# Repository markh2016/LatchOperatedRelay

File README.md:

# LatchOperatedRelay
Basic operating system requirements 

# PCB Layout

# Schematic Layout 

Cad software used  KICAD 

Version: 6.0.11+dfsg-1, release build
Libraries:
    wxWidgets 3.2.2
    libcurl/7.88.1 OpenSSL/3.0.9 zlib/1.2.13 brotli/1.0.9 zstd/1.5.4 libidn2/2.3.3 libpsl/0.21.2 (+libidn2/2.3.3) libssh2/1.10.0 nghttp2/1.52.0 librtmp/2.3
Platform: Linux 6.1.0-11-amd64 x86_64, 64 bit, Little endian, wxGTK, plasma, x11

Build Info:

    Date: Jan 26 2023 05:35:43
    wxWidgets: 3.2.1 (wchar_t,wx containers) GTK+ 3.24
    Boost: 1.74.0
    OCC: 7.6.3
    Curl: 7.87.0
    ngspice: 38
    Compiler: GCC 12.2.0 with C++ ABI 1017
Build settings:
    KICAD_USE_OCC=ON
    KICAD_SPICE=ON

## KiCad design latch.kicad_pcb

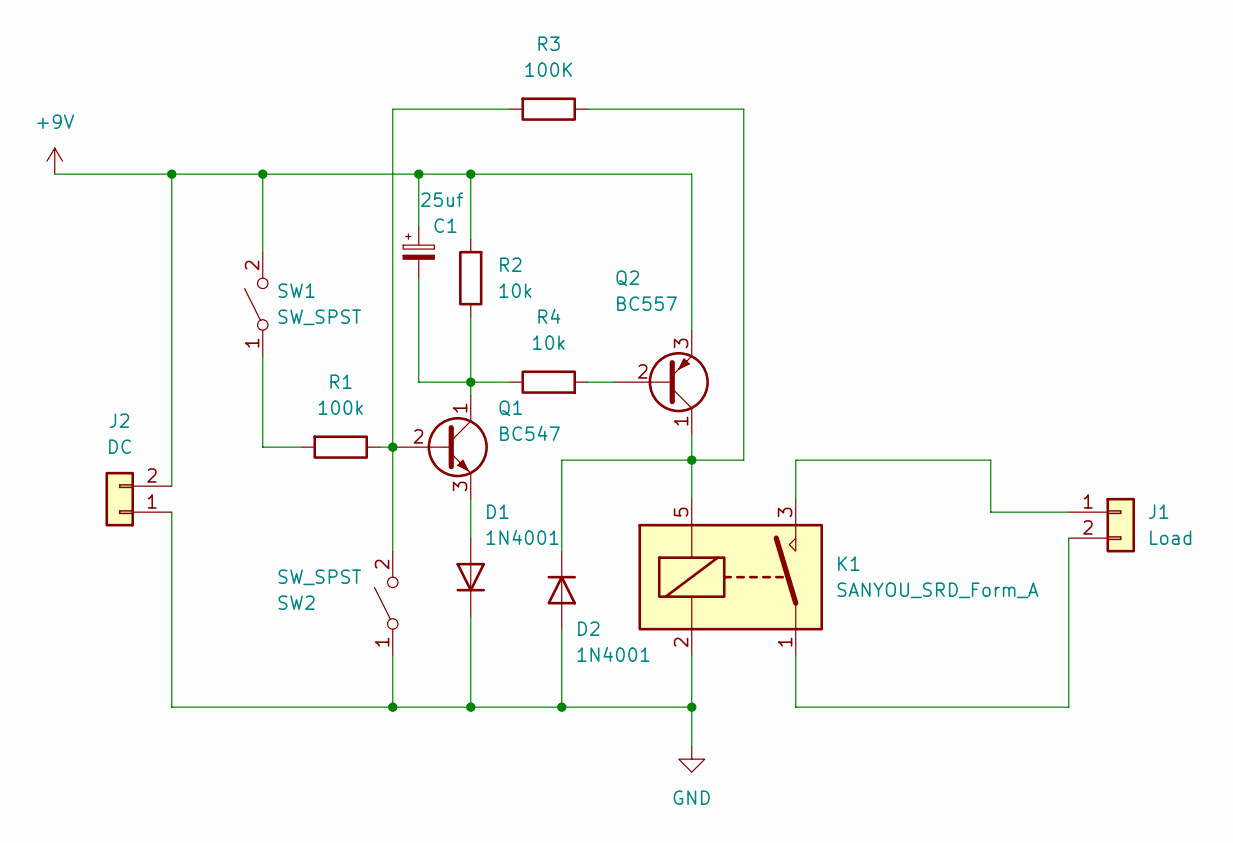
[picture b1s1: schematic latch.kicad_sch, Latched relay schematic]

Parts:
C1: 25uf; CP_Radial_D4.0mm_P2.00mm
D1, D2: 1N4001; D_DO-41_SOD81_P10.16mm_Horizontal
J1: Load; TerminalBlock_bornier-2_P5.08mm
J2: DC; TerminalBlock_bornier-2_P5.08mm
K1: SANYOU_SRD_Form_A; Relay_SPST_SANYOU_SRD_Series_Form_A
Q1: BC547; TO-92_Inline
Q2: BC557; TO-92_Inline
R1: 100k; R_Axial_DIN0204_L3.6mm_D1.6mm_P5.08mm_Horizontal
R2, R4: 10k; R_Axial_DIN0204_L3.6mm_D1.6mm_P5.08mm_Horizontal
R3: 100K; R_Axial_DIN0204_L3.6mm_D1.6mm_P5.08mm_Horizontal
SW1, SW2: SW_SPST; SW_SPST_Omron_B3F-315x_Angled

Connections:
+9V: C1.1, J2.2, Q2.3 (E), R2.2, SW1.2 (B)
GND: D1.1 (K), D2.2 (A), J2.1, K1.2, SW2.1 (A)
unnamed: C1.2, Q1.1 (C), R2.1, R4.1
unnamed: D1.2 (A), Q1.3 (E)
unnamed: D2.1 (K), K1.5, Q2.1 (C), R3.1
unnamed: J1.1, K1.3
unnamed: J1.2, K1.1
unnamed: Q1.2 (B), R1.1, R3.2, SW2.2 (B)
unnamed: Q2.2 (B), R4.2
unnamed: R1.2, SW1.1 (A)

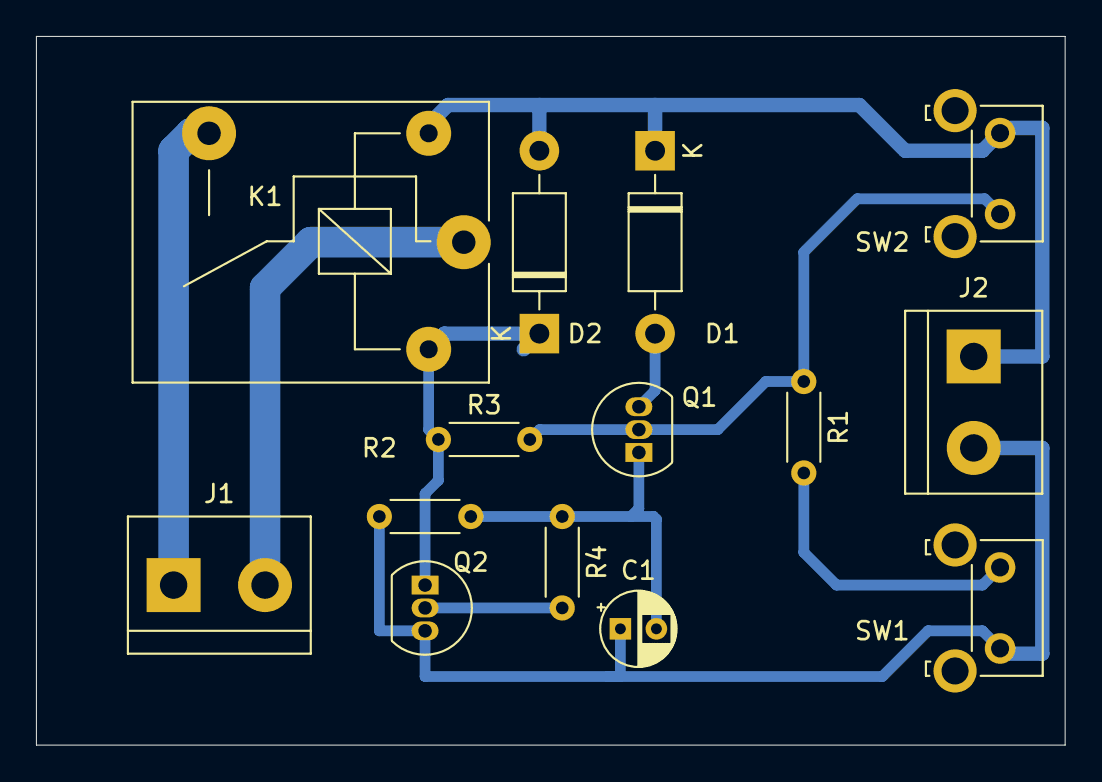
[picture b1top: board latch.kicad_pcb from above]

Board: 2 copper layers, 57.2 x 39.4 mm, 14 parts (0 on the bottom side), 10 nets.

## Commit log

2023-09-10 additional files that yu may need
